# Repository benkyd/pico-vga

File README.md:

# Pico-VGA: A micro controller video card

A VGA Driver made from a Raspberry Pi Pico with the eventual goal of being an acting video card.

I also plan to experiment with 3D rendering on it.

## PCB
Kicad and fabrication files can be found in `kicad/`

## Contributors
- [Alexandre Rouma](https://github.com/AlexandreRouma) (Logo Design)
- [Joshua Webster](https://github.com/w3bb0) (PCB Design)

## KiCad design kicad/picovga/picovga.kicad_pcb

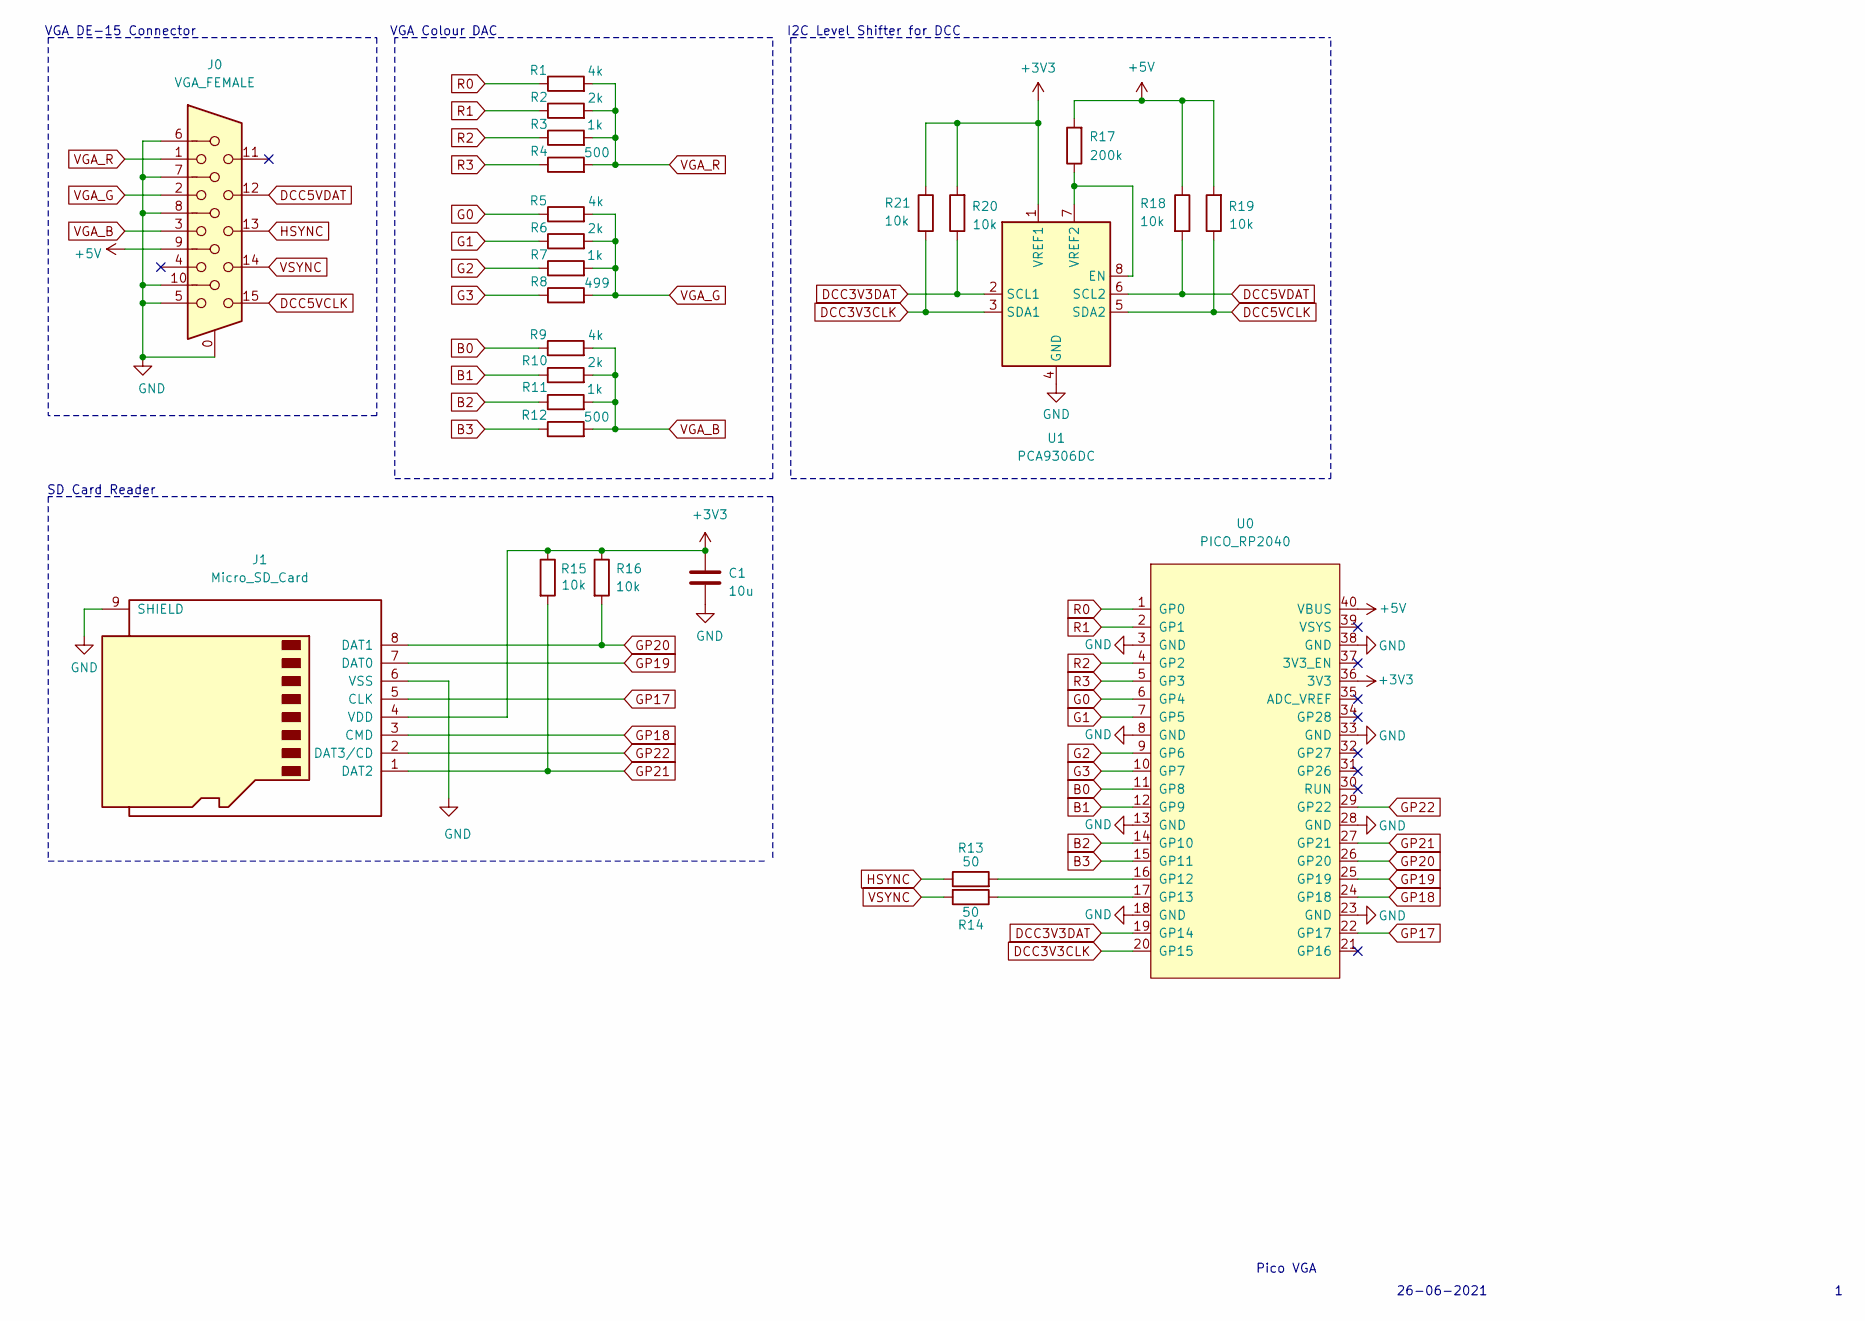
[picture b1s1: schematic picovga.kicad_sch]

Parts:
C1: 10u; C_0805_2012Metric_Pad1.18x1.45mm_HandSolder
J0: VGA_FEMALE; XM4L1542132
J1: Micro_SD_Card; microSD_HC_Hirose_DM3AT-SF-PEJM5
R1, R5, R9: 4k; R_0805_2012Metric_Pad1.20x1.40mm_HandSolder
R2, R6, R10: 2k; R_0805_2012Metric_Pad1.20x1.40mm_HandSolder
R3, R7, R11: 1k; R_0805_2012Metric_Pad1.20x1.40mm_HandSolder
R4, R12: 500; R_0805_2012Metric_Pad1.20x1.40mm_HandSolder
R8: 499; R_0805_2012Metric_Pad1.20x1.40mm_HandSolder
R13, R14: 50; R_0805_2012Metric_Pad1.20x1.40mm_HandSolder
R15, R16, R18, R19, R20, R21: 10k; R_0805_2012Metric_Pad1.20x1.40mm_HandSolder
R17: 200k; R_0805_2012Metric_Pad1.20x1.40mm_HandSolder
U0: PICO_RP2040; raspberrypi-pico-module
U1: PCA9306DC; VSSOP-8_2.3x2mm_P0.5mm

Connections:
+3V3: C1.1, J1.4 (VDD), R15.1, R16.1, R20.2, R21.1, U0.36 (3V3), U1.1 (VREF1)
+5V: J0.9, R17.2, R18.1, R19.2, U0.40 (VBUS)
B0: R9.1, U0.11 (GP8)
B1: R10.1, U0.12 (GP9)
B2: R11.1, U0.14 (GP10)
B3: R12.1, U0.15 (GP11)
DCC3V3CLK: R21.2, U0.20 (GP15), U1.3 (SDA1)
DCC3V3DAT: R20.1, U0.19 (GP14), U1.2 (SCL1)
DCC5VCLK: J0.15, R19.1, U1.5 (SDA2)
DCC5VDAT: J0.12, R18.2, U1.6 (SCL2)
G0: R5.1, U0.6 (GP4)
G1: R6.1, U0.7 (GP5)
G2: R7.1, U0.9 (GP6)
G3: R8.1, U0.10 (GP7)
GND: C1.2, J0.0, J0.5, J0.6, J0.7, J0.8, J0.10, J1.6 (VSS), J1.9 (SHIELD), U0.3 (GND), U0.8 (GND), U0.13 (GND), U0.18 (GND), U0.23 (GND), U0.28 (GND), U0.33 (GND), U0.38 (GND), U1.4 (GND)
GP17: J1.5 (CLK), U0.22 (GP17)
GP18: J1.3 (CMD), U0.24 (GP18)
GP19: J1.7 (DAT0), U0.25 (GP19)
GP20: J1.8 (DAT1), R16.2, U0.26 (GP20)
GP21: J1.1 (DAT2), R15.2, U0.27 (GP21)
GP22: J1.2 (DAT3/CD), U0.29 (GP22)
HSYNC: J0.13, R13.1
unnamed: R13.2, U0.16 (GP12)
unnamed: R14.1, U0.17 (GP13)
unnamed: R17.1, U1.7 (VREF2), U1.8 (EN)
R0: R1.1, U0.1 (GP0)
R1: R2.1, U0.2 (GP1)
R2: R3.1, U0.4 (GP2)
R3: R4.1, U0.5 (GP3)
VGA_B: J0.3, R9.2, R10.2, R11.2, R12.2
VGA_G: J0.2, R5.2, R6.2, R7.2, R8.2
VGA_R: J0.1, R1.2, R2.2, R3.2, R4.2
VSYNC: J0.14, R14.2
no_connect_34: J0.11
no_connect_35: J0.4
no_connect_36: U0.21 (GP16)
no_connect_37: U0.30 (RUN)
no_connect_38: U0.31 (GP26)
no_connect_39: U0.32 (GP27)
no_connect_40: U0.34 (GP28)
no_connect_41: U0.35 (ADC_VREF)
no_connect_42: U0.37 (3V3_EN)
no_connect_43: U0.39 (VSYS)

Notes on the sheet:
SD Card Reader
VGA DE-15 Connector
VGA Colour DAC
I2C Level Shifter for DCC
Pico VGA
26-06-2021

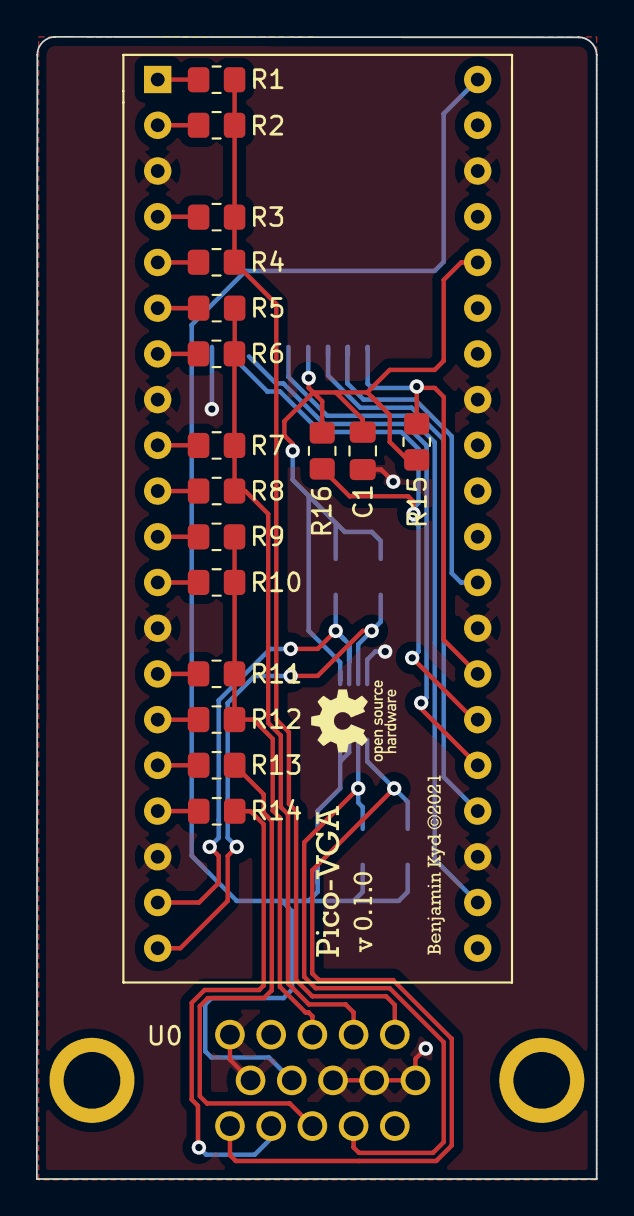
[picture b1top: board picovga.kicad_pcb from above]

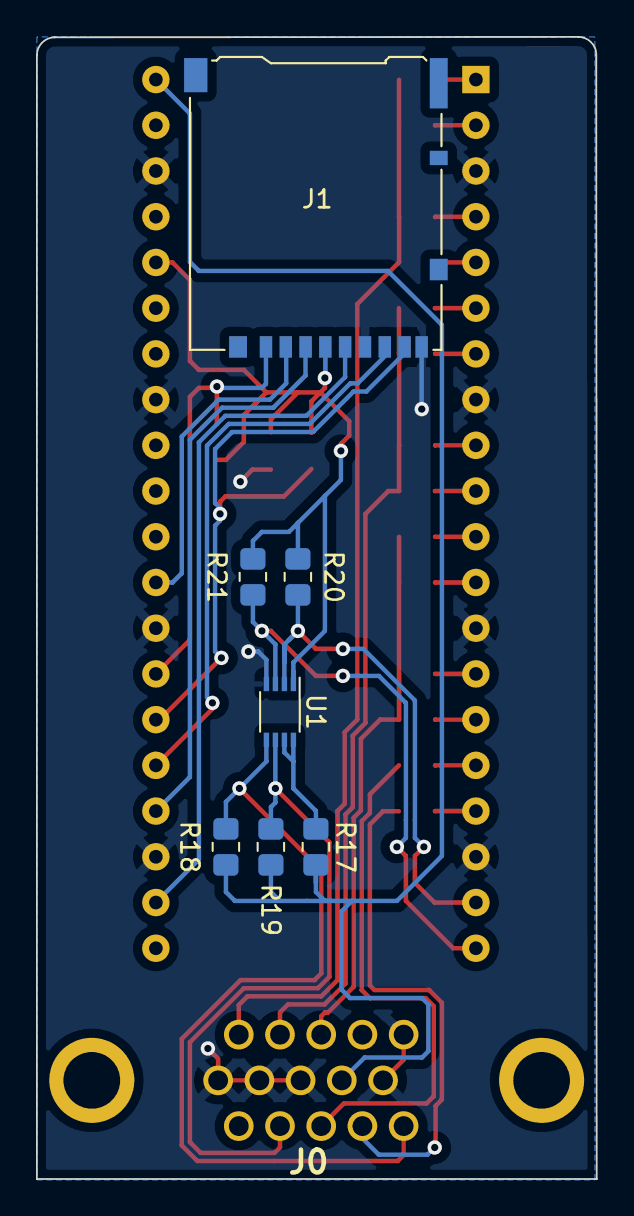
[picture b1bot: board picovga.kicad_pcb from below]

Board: 2 copper layers, 31.1 x 63.5 mm, 29 parts (8 on the bottom side), 33 nets.

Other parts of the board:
G: LOGO; name-logo
G#2: LOGO; product-version
G#3: LOGO; product-logo

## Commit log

2021-06-18 Modify picovga.c
2021-06-20 this is funky
2021-06-28 add KiCAD PCB Files and more pio code
2021-07-01 board off for fabrication
2021-07-01 Add readme
2021-07-01 fixed the error
2021-10-29 Create LICENSE
2023-06-09 Seeing if i can get this to work
